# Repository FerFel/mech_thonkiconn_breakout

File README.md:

# mech_thonkiconn_breakout
Breadboard Adapter for Thonkiconn Modular Jack

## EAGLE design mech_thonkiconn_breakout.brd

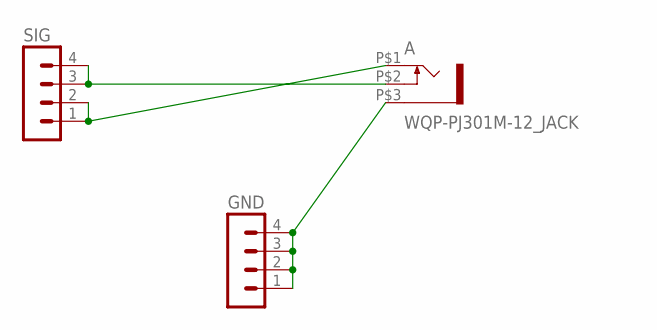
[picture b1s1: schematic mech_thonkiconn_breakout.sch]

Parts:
A: WQP-PJ301M-12_JACK
GND: MA04-1
SIG: MA04-1

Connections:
unnamed: A.P$1 (2), SIG.1, SIG.2
unnamed: A.P$3 (1), GND.1, GND.2, GND.3, GND.4
unnamed: A.P$2 (3), SIG.3, SIG.4

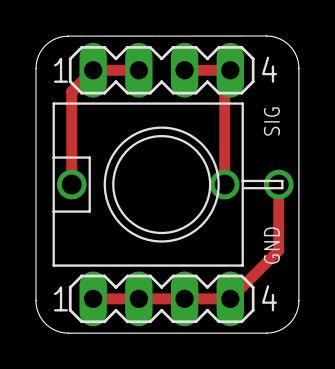
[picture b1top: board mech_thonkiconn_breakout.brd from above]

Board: 2 copper layers, 14.6 x 16.5 mm, 3 parts (0 on the bottom side), 3 nets.

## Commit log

2016-12-07 :space_invader: Added .gitattributes & .gitignore files
2016-12-07 added pcb png
